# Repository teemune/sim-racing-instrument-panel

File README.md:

# sim-racing-instrument-panel
 Instruments for sim racing games
 
## SimHub Gear Display
Design files for electronics and FW included.

Works with SimHub Dash Studio, which generates the Arduino code. Standard Arduino bootloader needs to be flashed on the microcontroller first, to make it able to receive a firmware through USB.

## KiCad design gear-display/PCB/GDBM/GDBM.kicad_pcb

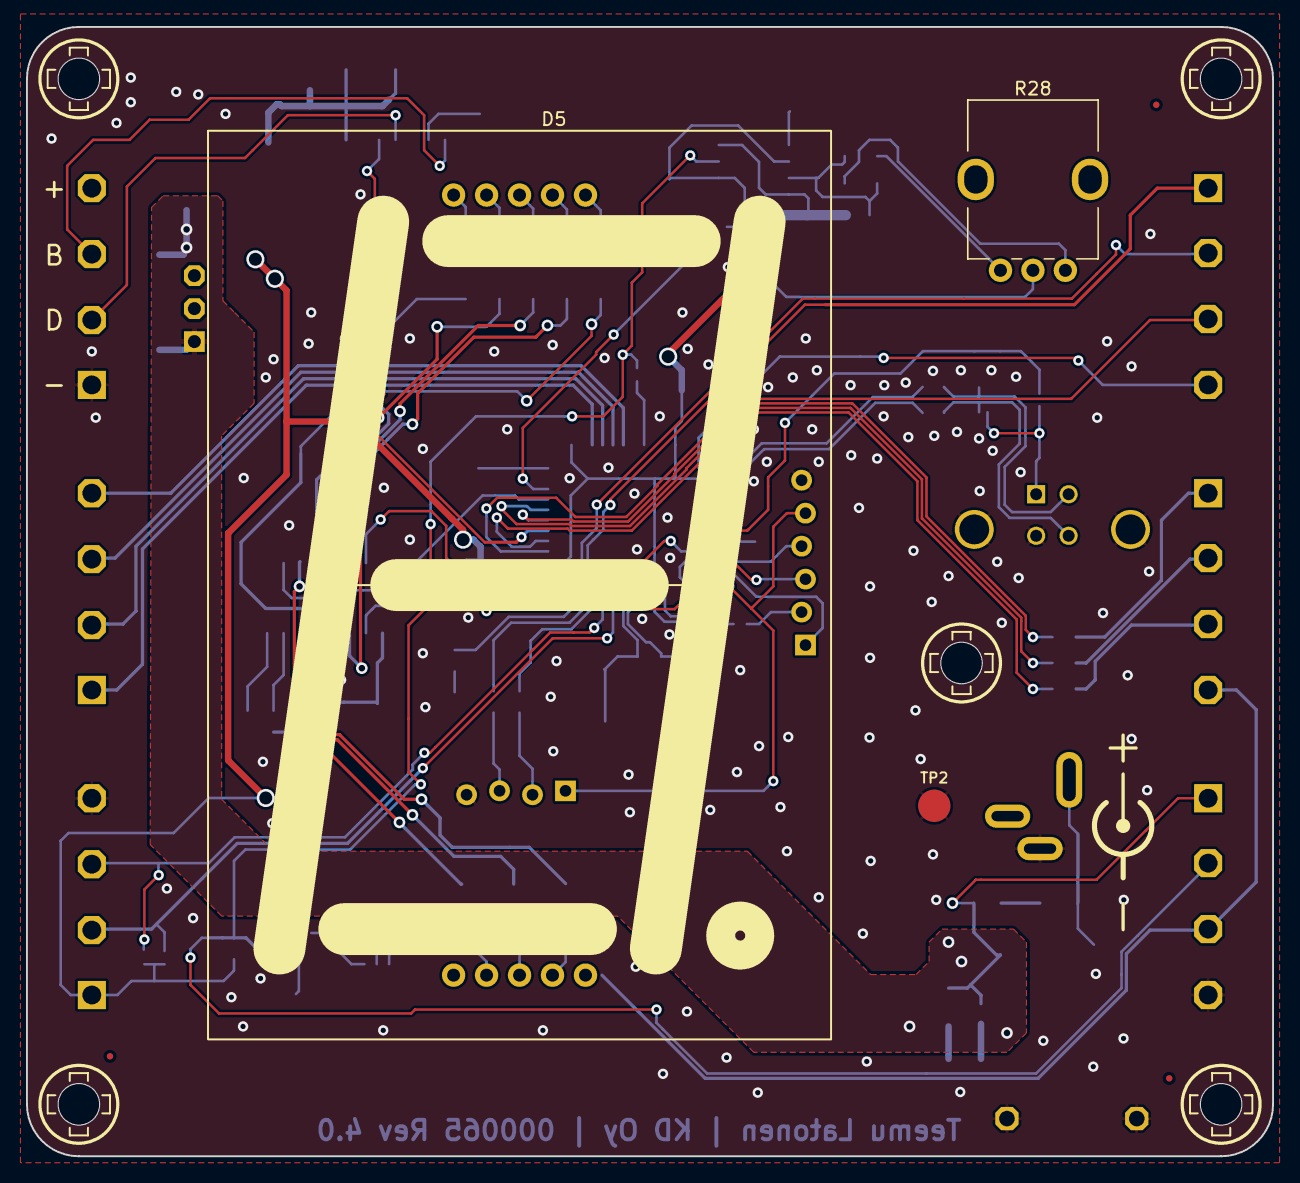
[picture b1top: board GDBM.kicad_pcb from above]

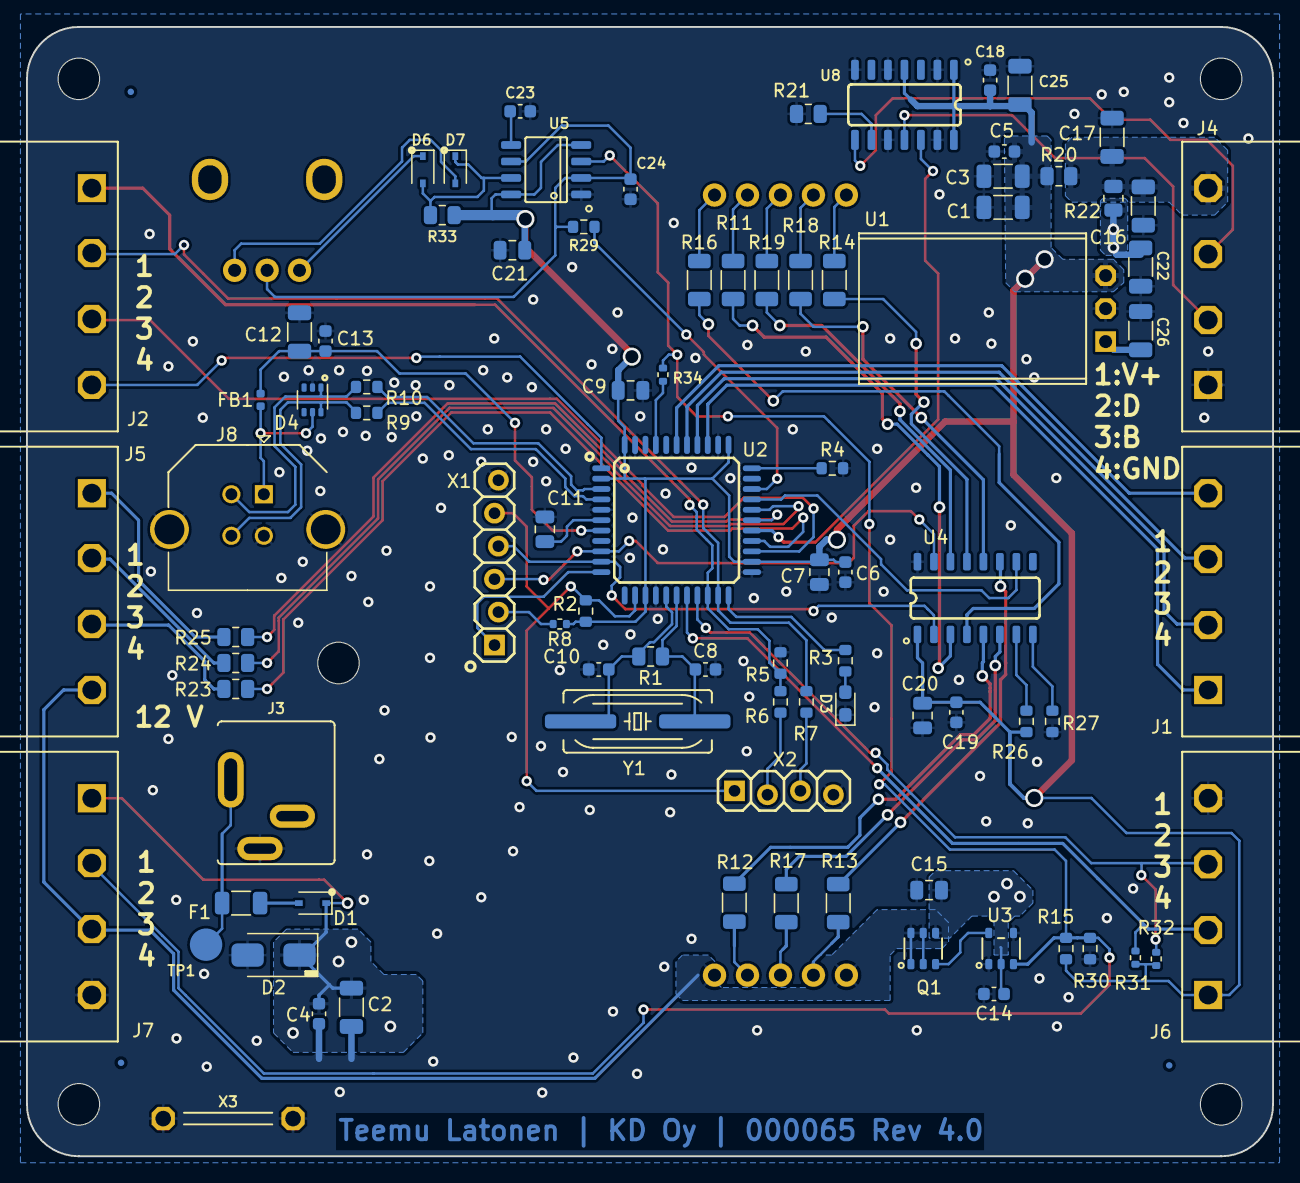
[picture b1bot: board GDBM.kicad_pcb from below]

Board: 2 copper layers, 96.0 x 87.0 mm, 103 parts (90 on the bottom side), 74 nets.

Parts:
ART1: Artwork_DC_Plug_Polarity; ART_DC_POLARITY
C1, C2, C3, C12, C16, C17, C22, C25, C26: 10u; CAPC3216X150N
C4, C5, C6, C13, C14, C18, C19: 100n; CAPC1608X90N
C7, C9, C11, C21: 1u; CAPC2012X135N
C8, C10: 33p; CAPC1608X90N
C15, C20: 0805; CAPC2012X135N_DNP
C23, C24: 10n; CAPC1608X90N
D1, D6, D7: Schottky_30V_1A_Toshiba_CUS10S30; D_SOD-323
D2: TVS_12V_LF_SMAJ12CA; DIOC530X280X230_SMA_A
D3: 0603_Green_Clear_LTST-C190KGKT; LEDM1608X70M
D4: TVS_5V5_DRTR5V0U4S-7-M; SOT-363_SC-70-6
D5: 7seg_70mm_CA_Lumex_LDS-AD16RI; 7seg_70mm_Kingbright_SC23-11SURKWA
F1: Fuse_1A_C1F_1; RESC3216X70N
FB1: Ferrite_250mA_Murata_BLM15HG102SN1D; INDC1005X55N
FD1, FD2, FD3, FD4, FD5, FD6: Fiducial 0.5 mm; Fiducial_0.5mm_Mask1mm
H1, H3, H4, H5, H6: NPTH 3.2 M3 Clearance; NPTH_3.2mm_M3_clearance
J1, J2, J4, J5, J6, J7: 1x04; CON_508_1X04_691313510004_Mated
J3: DC_2.1_5.5_54-00286; CON_DC_2.1_5.5_Tensility_54-00286
J8: USB Mini B; USB_B_Vertical_Adam_USB-B-S-VT
M1: Knob_6mm_BL_RED_CLIFF_CL170842CR; Knob_CLIFF_CL170842CR
Q1: PMOS_30V_4A1_SIL3407-TP; SOT95P280X120-6RN
R1, R22: DNP; RESC2012X60N_DNP
R2, R4, R15, R26, R27: R_0603_22k_1%; RESC1608X55N
R3, R6, R7: R_0603_360_1%; RESC1608X55N
R5, R29, R30: R_0603_DNP; RESC1608X55N_DNP
R8: R_0402_DNP; RESC1005X40N
R9, R10: R_0603_10_5%; RESC1608X55N
R11, R12, R13, R14, R16, R17, R18, R19: R_1206_191_1%; RESC3216X70N
R20, R21, R23, R24, R25: 0; RESC2012X60N
R28: PT01-D225D-A503; Potentiometer_CUI_PT01-DX20K2-XXXX
R31, R32, R34: 4k7; RESC1005X40N
R33: R_0805_110_5%; RESC2012X60N
TP1, TP2: TestPoint_2.5mm_Round; TestPoint_Pad_D2.5mm
U1: DC_DC_5V_2A0_GAPTEC_OKI-78SR-5_H; DC_DC_GAPTEC_OKI-78SR-5_H
U2: ATmega32U4-AU; QFP80P1200X1200X120-44R_N
U3: MCP1401; SOT95P280X145-5N
U4: Shift_register_OC_8bit_STPIC6D595MTR; SOIC127P640X200-16N
U5: Timer_Oscillator_TLC555CDG4; SOIC127P600X175-8
U8: Buffer_74LVC125AS14-13_DIODES; SOIC127P600X175-14N
X1: Programming_AVR_ISP_Staggered_Holes; CON_PINHD_1X06_TH_OFFSET
X2: CON_1x04_TH_staggered; CON_PINHD_1X04_TH_OFFSET
X3: GND Hook; GND_HOOK_M
Y1: 16 MHz; OSC_CRYSTAL_HC49_US_N

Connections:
+5V: C1.1, C3.1, C5.1, C6.1, C7.2, C9.1, C18.1, C19.1, C20.1, C21.1, C25.1, J6.1, R2.1, R8.1, R15.1, R20.1, R26.1, R31.1, R32.1, R33.1, U1.3 (VO), U2.2 (UVCC), U2.14 (VCC), U2.24 (AVCC), U2.34 (VCC1), U2.44 (AVCC1), U4.1 (VCC), U5.4 (R), U5.8 (VCC), U8.1 (~OE1), U8.4 (~OE2), U8.14 (V+)
+12V: C2.1, C4.1, C14.1, C15.1, C22.1, C26.1, D1.1 (K), D2.1 (K), J7.1, Q1.4 (S), R22.1, U1.1 (VI), U3.2 (VCC)
/7-Segment Display/12V_PWM: D5.1 (K), D5.5 (C), J5.4, J7.3, Q1.1 (D), Q1.2 (D), Q1.5 (D), Q1.6 (D)
/7-Segment Display/PWM: J7.2, R15.2, R30.1, R34.2, U3.3 (IN), U5.3 (Q)
/7-Segment Display/a: R11.1, U4.3 (DRAIN0)
/7-Segment Display/b: R16.1, U4.4 (DRAIN1)
/7-Segment Display/c: R12.1, U4.5 (DRAIN2)
/7-Segment Display/d: R17.1, U4.6 (DRAIN3)
/7-Segment Display/dp: R19.1, U4.14 (DRAIN7)
/7-Segment Display/e: R13.1, U4.11 (DRAIN4)
/7-Segment Display/f: R18.1, U4.12 (DRAIN5)
/7-Segment Display/g: R14.1, U4.13 (DRAIN6)
/Brightness Control/PWM_drive: R29.1, U2.31 (PC6(OC3A/~OC4A))
/Interfaces/SCL: J6.2, R31.2, U2.18 (PD0(INT0/OC0B/SCL))
/Interfaces/SDA: J6.3, R32.2, U2.19 (PD1(INT1/SDA))
/LED Driver 3/RCK: U2.30 (PB6(OC1B/OC4B/ADC13)), U4.10 (RCK)
/LED Driver 3/~CLR: R26.2, U4.7 (~CLR)
/LED Driver 3/~G: R27.1, U4.8 (~G)
/MCU/A0(D18): J1.1, U2.36 (PF7(ADC7(TDI))
/MCU/A1(D19): J1.2, U2.37 (PF6(ADC6/TDO))
/MCU/A2(D20): J1.3, U2.38 (PF5(ADC5/TMS))
/MCU/A3(D21): J1.4, U2.39 (PF4(ADC4/TCK))
/MCU/A5(D23): R34.1, U2.41 (PF0(ADC0))
/MCU/D0(RX): J2.1, R5.2, R6.1, U2.20 (PD2(INT2/RXD1))
/MCU/D1(TX): J2.2, R7.1, U2.21 (PD3(INT3/TXD1))
/MCU/D4: J2.3, U2.25 (PD4(ICP1/ADC8))
/MCU/D6: U2.27 (PD7(OC4D/ADC10/T0)), U8.12 (A4)
/MCU/D7: J2.4, U2.1 (PE6(INT.6/AIN0))
/MCU/D8: R25.2, U2.28 (PB4(ADC11))
/MCU/D9: R24.2, U2.29 (PB5(OC1A/ADC12/~OC4B))
/MCU/D12: R23.2, U2.26 (PD6(T1/ADC9/~OC4D))
/MCU/MISO: U2.11 (PB3(PDO/MISO)), X1.1 (MISO)
/MCU/MOSI: U2.10 (PB2(PDI/MOSI)), U4.2 (SER_IN), X1.4 (MOSI)
/MCU/SCLK: U2.9 (PB1(SCK)), U4.15 (SRCK), X1.3 (SCK)
/MCU/USB_D_N: R10.2, U2.3 (D-)
/MCU/USB_D_P: R9.2, U2.4 (D+)
/MCU/USB_VBUS: C12.1, C13.1, FB1.2, U2.7 (VBUS)
/MCU/X4_RXD: R6.2, X2.2
/MCU/X4_TXD: R7.2, X2.3
/MCU/~RESET: R2.2, U2.13 (~RESET), X1.5 (RST), X2.1
/RPM Bar/LED_PWR: C16.1, C17.1, J4.4, R20.2, R22.2
/RPM Bar/LED_STRIP_B: R21.1, U8.9 (A3)
/USB/USB_CON_D_N: D4.1, J8.2 (D-), R10.1
/USB/USB_CON_D_P: D4.6, J8.3 (D+), R9.1
Earth: C1.2, C2.2, C3.2, C4.2, C5.2, C6.2, C7.1, C8.2, C9.2, C10.2, C11.1, C12.2, C13.2, C14.2, C15.2, C16.2, C17.2, C18.2, C19.2, C20.2, C21.2, C22.2, C23.2, C24.1, C25.2, C26.2, D2.2 (A), D3.1 (K), D4.2 (V-), J3.B (SLEEVE), J4.1, J6.4, J7.4, J8.4 (GND), J8.H1 (Shield), J8.H2 (Shield), R4.2, R5.1, R21.2, R27.2, R30.2, TP2.1, U1.2 (GND), U2.5 (UGND), U2.15 (GND), U2.23 (GND1), U2.35 (GND2), U2.43 (GND3), U3.1 (GND), U3.4 (GND), U4.16 (GND), U5.1 (GND), U8.2 (A1), U8.5 (A2), U8.7 (GND), U8.10 (~OE3), U8.13 (~OE4), X1.6 (GND), X2.4, X3.1, X3.2 (Pin_1)
unnamed: D1.2 (A), F1.2
unnamed: D3.2 (A), R3.1
unnamed: D4.5 (V+), FB1.1, J8.1 (VBUS)
unnamed: D5.7 (Aa), R11.2
unnamed: D5.6 (Ab), R16.2
unnamed: D5.4 (Ac), R12.2
unnamed: D5.3 (Ad), R17.2
unnamed: D5.8 (Adp), R19.2
unnamed: D5.2 (Ae), R13.2
unnamed: D5.9 (Af), R18.2
unnamed: D5.10 (Ag), R14.2
unnamed: D6.2 (A), D7.1 (K), R33.2, U5.7 (DIS)
unnamed: D6.1 (K), R28.3
unnamed: D7.2 (A), R28.1
unnamed: F1.1, J3.A (CENTER), TP1.1
unnamed: J4.2, U8.11 (Y4)
unnamed: J4.3, U8.8 (Y3)
unnamed: J5.1, R25.1
unnamed: J5.2, R24.1
unnamed: J5.3, R23.1
unnamed: Q1.3 (G), U3.5 (OUT)
unnamed: R3.2, U2.22 (PD5(XCK/CTS))
unnamed: R4.1, U2.33 (PE2(~HWB))
unnamed: C11.2, U2.6 (UCAP)
unnamed: C8.1, R1.1, U2.17 (XTAL1), Y1.1
unnamed: C10.1, R1.2, U2.16 (XTAL2), Y1.2
unnamed: C23.1, U5.5 (CV)
unnamed: C24.2, R28.2, R29.2, U5.2 (TR), U5.6 (THR)
unnamed: R8.2, X1.2 (VCC)

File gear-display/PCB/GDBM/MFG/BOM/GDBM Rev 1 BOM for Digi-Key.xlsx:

Item | Qty | Reference(s) | Code | DNP | MFG_PartNo | Manufacturer | Price | Supplier | Supplier_PartNo |  | Reference
1 | 7 | C1, C2, C3, C12, C16, C17, C18 | 10 uF | F | CL31B106KBHNNNE | Samsung Electro-Mechanics | 0.1 | Digi-Key | 1276-6767-1-ND |  | Gear Display
2 | 6 | C4, C5, C6, C13, C14, C19 | 100n | F | CL10B104KC8NNNC | Samsung Electro-Mechanics | 0.03 | Digi-Key | 1276-6807-1-ND |  | Gear Display
3 | 4 | C7, C9, C11, C21 | 1u | F | CL21B105KAFNNNE | Kemet | 0.03 | Digi-Key | 1276-1066-1-ND |  | Gear Display
4 | 2 | C8, C10 | 33p | F | C0603C330J1GAC7867 | KEMET | 0.05 | Digi-Key | 399-C0603C330J1GAC7867CT-ND |  | Gear Display
6 | 1 | D1 | CUS10S30,H3F | F | CUS10S30,H3F | Toshiba Semiconductor and Storage | 0.2 | Digi-Key | CUS10S30H3FCT-ND |  | Gear Display
7 | 1 | D2 | SMAJ12A | F | SMAJ12A | Littelfuse Inc. | 0.3 | Digi-Key | SMAJ12ALFCT-ND |  | Gear Display
8 | 1 | D3 | Green Clear | F | LTST-C190KGKT | Lite-On Inc. | 0.05 | Digi-Key | 160-1435-1-ND |  | Gear Display
9 | 1 | D4 | DRTR5V0U4S-7 | F | DRTR5V0U4S-7 | Diodes Incorporated | 0.3 | Digi-Key | DRTR5V0U4S-7DICT-ND |  | Gear Display
10 | 1 | D5 | LDS-AD16RI | F | LDS-AD16RI | Lumex Opto/Components Inc. | 13 | Digi-Key | 67-1493-ND |  | Gear Display
11 | 1 | F1 | Fuse 1 A | F | C1F 1 | Bel Fuse Inc. | 0.15 | Digi-Key | 507-1878-1-ND |  | Gear Display
12 | 1 | FB1 | BLM15HG102SN1D | F | BLM15HG102SN1D | Murata Electronics | 0.1 | Digi-Key | 490-3999-1-ND |  | Gear Display
14 | 6 | J1, J2, J4, J5, J6, J7 | 1x04 | F | 691313510004 | WÃ¼rth Elektronik | 0.3 | Digi-Key | 732-2072-ND |  | Gear Display
15 | 1 | J3 | 2.5 mm DC | F | PJ-090BH | CUI Devices | 1.7 | Digi-Key | 102-5562-1-ND |  | Gear Display
16 | 1 | J8 | USB Mini B | F | USB-B-S-VT | Adam Tech | 1 | Digi-Key | 2057-USB-B-S-VT-ND |  | Gear Display
17 | 1 | M1 | CL170842CR | F | CL170842CR | CLIFF Electronic Components Ltd | 1 | Digi-Key | 3185-CL170842CR-ND |  | Gear Display
18 | 1 | Q1 | SIL3407-TP | F | SIL3407-TP | Micro Commercial Co | 0.4 | Digi-Key | 353-SIL3407-TPCT-ND |  | Gear Display
20 | 5 | R2, R4, R15, R26, R27 | 22k | F | 311-22.0KHRCT-ND | YAGEO | 0.01 | Digi-Key | 311-22.0KHRCT-ND |  | Gear Display
21 | 3 | R3, R6, R7 | 360 | F | RT0603FRE07360RL | YAGEO | 0.02 | Digi-Key | 13-RT0603FRE07360RLCT-ND |  | Gear Display
24 | 2 | R9, R10 | 10 | F | WR06X100 JTL | Walsin Technology Corporation | 0.01 | Digi-Key | 1292-WR06X100JTLCT-ND |  | Gear Display
25 | 8 | R11, R12, R13, R14, R16, R17, R18, R19 | 191 | F | RC1206FR-07191RL | YAGEO | 0.05 | Digi-Key | 311-191FRCT-ND |  | Gear Display
26 | 5 | R21, R22, R23, R24, R25 | 0 | F | RMCF0805ZT0R00 | Stackpole Electronics Inc | 0.01 | Digi-Key | RMCF0805ZT0R00CT-ND |  | Gear Display
27 | 1 | R28 | PT01-D120K2-B103 | F | PT01-D120K2-B103 | CUI Devices | 0.77 | Digi-Key | 2223-PT01-D120K2-B103-ND |  | Gear Display
28 | 3 | R29, R31, R32 | 4k7 | F | CR0402-FX-4701GLF | Bourns Inc. | 0.01 | Digi-Key | CR0402-FX-4701GLFCT-ND |  | Gear Display
29 | 1 | U1 | K78U05-500R3 | F | K78U05-500R3 | Mornsun America, LLC | 3 | Digi-Key | 2725-K78U05-500R3-ND |  | Gear Display
30 | 1 | U2 | ATMEGA32U4-AU | F | ATMEGA32U4-AU | Microchip Technology | 5.3 | Digi-Key | ATMEGA32U4-AU-ND |  | Gear Display
31 | 1 | U3 | MCP1401 | F | MCP1401T-E/OT | Microchip Technology | 0.7 | Digi-Key | MCP1401T-E/OTCT-ND |  | Gear Display
32 | 1 | U4 | STPIC6D595MTR | F | STPIC6D595MTR | STMicroelectronics | 0.9 | Digi-Key | 497-6329-1-ND |  | Gear Display
35 | 1 | Y1 | 16 MHz | F | AS-16.000-18-SMD-TR | Raltron Electronics | 0 | Digi-Key | 2151-AS-16.000-18-SMD-TRCT-ND |  | Gear Display

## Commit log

2022-08-07 initial
2022-08-09 new features
2022-08-12 changed to match simhub conf
2022-08-13 rikki
2022-08-13 maybe ok
2022-08-17 PSU and LED powering changed
2022-08-17 PSU fixes
2022-08-26 Prototype v1
2022-09-10 fixes
2022-11-19 FW added
2022-12-06 changed location
2023-01-05 bugfixes
    added 555 circuit for brightness control
2023-01-05 layout
2023-02-05 Added a ferrite and silk screen markings
2023-02-05 RPM indicators added to FW
2023-02-26 BOM generated
2023-02-28 led buffer added
2023-03-01 documentation
2023-03-03 change to kicad 7
2023-03-18 new kicad version
2023-03-19 Update GDBM Rev 2.00 BOM ibom.html
    populated
2023-03-27 LED order changed again
2023-03-27 updated hw config
2023-03-27 FW to match PCB 2.0
2023-03-27 Documentation update
2023-03-27 Schematic pdfs added
2023-03-29 FW update
2023-03-29 FW update for rev2
2023-03-29 R33 value change
2023-03-29 RGB led count increased
2023-04-06 Revert "documentation update"
    This reverts commit 76ec955dce09cc544308a8dd0d1d241e10a4399a.
2023-05-28 Laser cut vectors
2023-10-09 version numbering fix
2024-07-11 Documentation and version update
